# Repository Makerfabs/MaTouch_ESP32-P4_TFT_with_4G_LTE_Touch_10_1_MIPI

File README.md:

# MaTouch ESP32-P4 TFT with 4G LTE Touch 10.1“ MIPI

## Introduction

The MaTouch ESP32-P4 TFTTouch 10.1" MIPI with 4G LTE SIM7670G is an upgraded high-resolution, all-in-one HMI solution designed for smart control systems, industrial dashboards, remote IoT terminals, and AI-enabled applications. This module integrates a powerful ESP32-P4 processor, built-in SIM7670G 4G LTE Cat.1 module, a crystal-clear 10.1" IPS display, full multimedia support, and robust multi-mode wired/wireless connectivity, all inside a refined, ready-to-use enclosure.

Powered by the RISC-V dual-core ESP32-P4 (400MHz) with 16MB Flash and 32MB PSRAM, the system handles complex UIs, LVGL rendering, and real-time multimedia tasks with ease. The independent ESP32-C6 wireless module adds Wi-Fi 6 and Bluetooth LE support for reliable, modern IoT connectivity, while the onboard 4G LTE module enables stable data transmission without local Wi-Fi or Ethernet coverage.

One of the standout features is the stunning 10.1-inch 1280×800 IPS MIPI display, offering sharp visuals, vibrant colors, and smooth touch interaction—ideal for both consumer-facing interfaces and professional industrial panels.Integrated 2MP MIPI camera (SC2336) delivers high-definition image capture, suitable for facial recognition, monitoring, visual interaction, and embedded AI vision tasks. With onboard microphone input, the device is also well-prepared for far-field voice control or audio-enabled applications. For stable and high-speed communication, the device features built-in Ethernet (IP101GRI)—making it suitable for industrial environments where wireless alone is not reliable.A refined protective enclosure allows developers to deploy the device quickly without additional mechanical design. Each unit also comes with a MicroSD card pre-included, enabling logs, multimedia storage, and rapid local data processing right out of the box.

Product Link: [MaTouch ESP32-P4 TFT with 4G LTE Touch 10.1“ MIPI](https://www.makerfabs.com/matouch-esp32-p4-tfttouch-10-1-mipi-with-4g-lte-sim7670g.html)

Wiki Link:  [MaTouch ESP32-P4 TFT with 4G LTE Touch 10.1“ MIPI](https://wiki.makerfabs.com/MaTouch%20ESP32_P4%20TFT%20with%204G%20LTE%20Touch%2010.1%E2%80%9C%20MIPI.html)

Example：1.[4G_LTE_HTTP_Test](https://github.com/Makerfabs/MaTouch_ESP32-P4_TFT_with_4G_LTE_Touch_10_1_MIPI#4g_lte_http_test)

## Features

- Controller: ESP32-P4NRW32X
- Flash: 16MB Flash
- PSRAM: 32MB
- Wireless: 2.4GHz Wi-Fi 6 (802.11ax)，Bluetooth® 5 (LE)(ESP32-C6FH4)
- LCD: 10.1", 1280x800 resolution
- LCD Driver: JD9365
- LCD interface: MIPI
- Touch Panel: 5 Points Touch, Capacitive
- Touch Panel Driver: GT911
- USB: 1 * USB to UART, 1 * USB_NATIVE, 1 * USB_CDC/JTAG, 1 * USB_OTG, 1 * USB_DEVICE,
- Power Supply: USB Type-C 5.0V(4.0V~5.25V)
- Button: Flash button and reset button
- Camera Maximum Resolution: 2 Million Pixels, 1920H×1080V
- Camera Driver: SC2336
- Camera interface: MIPI
- Ethernet: IP101GRI
- 4G LTE: SIM7670G
- 4G Category: TDD/FDD-LTE CAT.1
- Data rate: 10 Mbps (DL),5 Mbps (UL)
- LTE-FDD Bands: B1/B2/B3/B4/B5/B7/B8/B12/B13/B18 /B19/B20/B25/B26/B28/B66/B71
- LTE-TDD Bands: B34/B38/B39/B40/B41
- Microphone input: Yes
- Audio output: ES8311
- MicroSD: Yes
- Charger: Yes
- Battery Connector: Yes
- Expansion interface: 26 * GPIO
- Arduino support: Yes
- LVGL support: Yes

## Example

### 4G_LTE_HTTP_Test

For details of this example, please refer to the [Wiki](https://wiki.makerfabs.com/MaTouch%20ESP32_P4%20TFT%20with%204G%20LTE%20Touch%2010.1%E2%80%9C%20MIPI.html#54g_lte_http) document.

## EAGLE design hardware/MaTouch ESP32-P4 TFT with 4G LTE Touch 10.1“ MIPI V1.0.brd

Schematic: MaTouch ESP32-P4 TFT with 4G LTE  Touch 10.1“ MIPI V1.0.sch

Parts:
1V8, 3V: TEST-POINT'4545'; TP-D45MIL; PARTNO DNP
BAT: JST-2P; HW2-SMD-2.0-90D
BAT1: CR1220SMT; CR1220-SMD
BOOT: TS24CA; 2*4*3.5MM
BOOT1: MOMENTARY-SWITCH-SPST-SMD-6.0X3.5MM; TACTILE_SWITCH_SMD_6.0X3.5MM
C1, C93, C94, C95, C96, C121, C124, C125, C126, C127, C128, C129, C130, C135, C140, C141: 1uF/16V; 0603
C2: 10pF/50V; DISCRETE_C0603
C3, C4, C6, C10, C16, C23, C29, C46, C54: 10uF; DISCRETE_C0603
C5, C21, C22, C28, C31, C34, C35, C42, C43, C48, C62, C65, C71, C74, C76, C78, C80, C83, C89, C97, C102, C107, C110, C114, C137, C142, C152, C165, C168, C170, C172, C174, C176, C178, C180, C182, C191, C193, C196, C220, C225, C227: 10uF; 0603
C6_BOOT, C6_RST: MOMENTARY-SWITCH-SPST-SMD-4.6X2.8MM; TACTILE_SWITCH_SMD_4.6X2.8MM
C6_EN, C6_IO9, C6_U0RXD, C6_U0TXD: PAD-TEST-POINT-CIRCLE'4545'; TP_4545; PARTNO DNP
C7, C8, C14, C17, C18, C19, C24, C26, C30, C32, C47, C60, C66, C108, C158, C185: 0.1uF; DISCRETE_C0603
C9, C51, C67, C72, C73, C75, C77, C79, C81, C84, C90, C91, C92, C98, C99, C100, C103, C104, C105, C106, C109, C111, C115, C131, C132, C138, C139, C143, C145, C147, C150, C153, C154, C155, C166, C169, C171, C173, C175, C177, C179, C181, C183, C192, C200, C203, C207, C209, C221, C222, C223, C224, C226: 0.1uF; 0603
C11: 4.7uF/35V; DISCRETE_C1206
C12: 0.1uF/50V; DISCRETE_C0603
C13: NC; DISCRETE_C0603
C15: 100nF; DISCRETE_C0603
C20, C25, C27, C41, C64, C136, C184: 4.7uF/16V; 0603
C33, C148, C149: 330pF/50V; 0603
C45, C53, C55, C205: NC; 0603
C49, C50, C63, C101, C194, C197, C206, C208: 1uF; 0603
C52: 1nF; 0603
C61, C190, C199, C202, C219: 33pF; 0603
C68: NC; DISCRETE_C1206
C69, C70, C116, C117: 12pF; DISCRETE_C0402
C82: 10nF; 0603
C85, C86: 20pF; DISCRETE_C0603
C87, C88: 15pF; DISCRETE_C0603
C118, C119, C120, C122, C123, C133, C134, C144, C146, C151, C167: 22pF; 0603
C156, C157: 1nF/50V; 0603
C159: 100nF; C0402
C160, C161: 10uF; C0603
C162, C163: 33pF; C0603
C164: 100nF; C0603
C195, C204: 100uF; EIA3528
C198: 100pF; 0603
C201: 10pF; 0603
C210, C211, C212: 22pF_NC; 0603
CHRG: RED; CHIPLED_0805_NOOUTLINE
CSI_RST: MOMENTARY-SWITCH-SPST-SMD-4.6X2.8MM; TACTILE_SWITCH_SMD_4.6X2.8MM
D1: 1N4148WS; SOD323
D2, D7, D13: 0603ESDA-05N; DISCRETE_SOD523
D3, D8: 5.1V; SOD-323
D4, D10: SMF05C; SOT363
D5, D12: SS54; DO-214AC
D6: B5819WS; SOD323
D+: TEST-POINT'4545'; TP-D45MIL; PARTNO DNP
D-: TEST-POINT'4545'; TP-D45MIL; PARTNO DNP
DONE: GREEN; CHIPLED_0805_NOOUTLINE
FB1, FB2, FB3, FB4, FB5: INDUCTORFB-30OHM; 0603
GPS: ANTENNA-U-FL; 4P-U-FL
IO34, IO35, IO36, IO37, IO38: TEST-POINT'4545'; TP-D45MIL; PARTNO DNP
J1, J2: GROVE-CONNECTOR-SMD'90D'; HW4-SMD-2.0-90D
J3: XH2.54-2P
J4: FPC-24P; SMD26-50P-1760L450W
J6, J10: CON2X20-254P-A; SMD2X20-254P-5080L750W920H
J7: HR961160C
J8: CON31-30P-A; SMD31-30P-1090L320W100H
L1: 10µH/±30%; CR54
L2: 4.7µH/±20%/3A; SRN6045
L3, L4: 2.2µH/±30%/3.4A; CR54
L5: BLM18BD252SN1; L0603
L6: 68nH; L0603
L7: 10µH/±20%/3.2A; CR54
LTE: ANTENNA-U-FL; 4P-U-FL
M1, M2, M3, M4, M5, M6, M7, M8, M9: M2.5
MIC: SAO-3729-M-42-008; MIC4-SMD-3.76X2.95MM
NET: NET; CHIP-LED0805
P1: DEBUG6; DEBUG*6
P2, P4: AFC01-S06FCC-00; SMD8-50P-740L535W
PWK: MOMENTARY-SWITCH-SPST-SMD-6.0X3.5MM; TACTILE_SWITCH_SMD_6.0X3.5MM
PWR: GREEN; CHIPLED_0805_NOOUTLINE
PWR1: JS102011JAQN; SMD-6-2.5MM
Q1, Q5, Q6, Q10, Q13, Q16, Q21, Q24: MOSFET-PCHANNEL; SOT23-3
Q2: 32.768K; XTAL3215
Q3, Q4, Q7: S8050; SOT23
Q8, Q9, Q11, Q12, Q14, Q15, Q17, Q18, Q22, Q23, Q25, Q26, Q27, Q28: 600mA/40V; SOT23-3
Q19, Q20: BS138; SOT23
Q29, Q32: BC847C; SOT23
Q30, Q31, Q33, Q34, Q35, Q36: 2N7002; SOT23
R1, R39, R44, R58, R60, R69, R70, R108, R156, R157, R158, R159, R172, R174, R176, R180, R191, R193: 10K; DISCRETE_R0603
R2, R17, R35, R41, R56, R63, R64, R68, R74, R75, R76, R77, R78, R79, R80, R81, R82, R83, R84, R89, R90, R91, R92, R93, R94, R96, R97, R98, R99, R100, R102, R109, R124, R125, R126, R127, R128, R129, R133, R134, R135, R136, R137, R144, R147, R153, R154, R155, R163, R167, R168, R170, R171, R184, R185, R217, R232, R235: 0R; R0603
R3, R46, R196: NC; R0603
R4, R6, R7, R8, R9, R55, R57, R173, R175, R177, R181, R186, R187, R188, R189, R190, R192, R194, R195: 51K; DISCRETE_R0603
R5, R31, R36, R37, R42, R47, R149, R160, R161: NC; DISCRETE_R0603
R10: 33K; R0603
R11, R24: 200K; R0603
R12, R13, R14, R15, R27, R38, R51, R53, R72, R73: 5.1K; DISCRETE_R0603
R16, R22, R25, R26, R66, R139, R143, R151, R164, R222, R224, R226, R228: 10K; R0603
R18, R67, R145: 100K; R0603
R19: 1.2K; DISCRETE_R0603
R20, R21, R40, R45, R54, R65, R71, R85, R86, R101, R110, R111, R112: 33R; R0603
R23: 50R; DISCRETE_R0603
R29, R218, R238: 1.2K; R0603
R30, R34, R103, R104, R105, R106, R107, R219: 100R; R0603
R32, R33: 3.6R; DISCRETE_R0603
R43, R169: 499K/NC; R0603
R48, R182: 3.3K; R0603
R49, R200, R215, R220: 47K; R0603
R50: 680K; R0603
R52: 470K; R0603
R59: 4.7K; DISCRETE_R0603
R87, R178, R179: 1.5K; R0603
R88: 1.5K/NC; R0603
R95, R150: 4.02K; R0603
R113, R116, R118, R120, R122, R123, R210, R211: 5.1K; R0603
R114, R115, R117, R119, R130: NC/5.1K; R0603
R121: 6.19K; R0603
R131, R132: NC/10K; R0603
R138: 10K/NC; R0603
R140: 200R; R0603
R141: 10R; R0603
R142: 0R/NC; R0603
R146: 22.1K; R0603
R148, R152, R162, R183, R197, R198: 2.2K; R0603
R165, R166, R244: 150K; R0603
R199, R214: 4.7K; R0603
R207, R208, R209, R212, R213: 22R; R0603
R216, R230, R231: 1K; R0603
R221, R223, R225, R227: 30K; R0603
R236, R237: 0.4R; 1206
R239: 50K; R0603
R240: 3R; R0603
R241, R242: 0.1R; DISCRETE_R2512
R243: 5.76K; R0603
RST: TS24CA; 2*4*3.5MM
RX: TEST-POINT'4545'; TP-D45MIL; PARTNO DNP
SD: HOLDER-MICROSD-9P; 9P-SMD-W/-RING
SIM: MICROSIM
SPK: 1X2P; 1X2P-SMT1.25MM
STA: NET; CHIP-LED0805
TX: TEST-POINT'4545'; TP-D45MIL; PARTNO DNP
U1: ESP32-C6-MINI-1
U2: RY3730; SOT23-6
U3: CH340K; ESOP-10-EP-150MIL
U4: MP2143DJ-LF-Z; TSOT23-8
U5, U10, U14, U15, U16: SPX3819; SOT23-5
U7: AMS1117-3.3V; SOT89
U8: ESP32-P4; QFN105-35P-500L500W
U9: W25Q128JV; SOIC-8-208MIL
U11, U17: TLV62569DBVR; SOT23-5-95P-300L300W
U12: ES8311; QFN20-40P-300L300W55H
U13: IP101GRI; QFN32-40P-400W400L
U18: A7670G
U19: TP5100; QFN17-65P-400L400W80H
U20: NS4150B; MSOP8-65P-490L300W110H
UN: PAD-TEST-POINT-CIRCLE'4545'; TP_4545; PARTNO DNP
UP: PAD-TEST-POINT-CIRCLE'4545'; TP_4545; PARTNO DNP
USB-CDC/JTAG: USB_C5; USB-C-16P-5
USB-DEVICE: USB_C5; USB-C-16P-5
USB-LTE: USB_C5; USB-C-16P-5
USB-NATIVE: USB_C5; USB-C-16P-5
USB-OTG: USB_C5; USB-C-16P-5
USB-TTL: USB_C5; USB-C-16P-5
VPWR: PAD-TEST-POINT-CIRCLE'4545'; TP_4545; PARTNO DNP
X1: 40MHz(10ppm); NX3225
X2: 25MHz(10ppm); NX3225
X3: 24MHz; OSC4-SMD-2.5X2.0X0.8MM

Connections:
1.8V: 1V8.T, C208.2, C209.2, D6.+, Q33.1 (G), Q34.1 (G), Q35.1 (G), Q36.1 (G), R222.2, R224.2, R226.2, R228.2, U18.15 (VDD_EXT), U18.97 (NC)
3.3V: C5.1, C9.1, C16.2, C17.2, C22.1, C23.2, C24.2, C29.2, C30.2, P1.1, R1.2, R36.2, R42.2, R44.2, R47.2, R57.2, R63.2, R66.2, R67.2, R155.1, R186.2, R187.2, R188.2, R189.2, R190.2, U1.3 (3V3)
25M_XI: C117.2, U13.2 (X1), X2.3 (X2)
25M_XO: C116.1, U13.3 (X2), X2.1 (X1)
+3V3: C3.2, C18.2, C19.2, C20.1, C25.1, C27.1, C42.1, C46.2, C47.2, C60.2, C66.2, C159.2, C184.1, C185.2, J1.3, J2.3, J8.1, J8.2, J8.3, J8.6, P2.5, P4.1, PWR.A, R22.2, R48.2, R63.1, R149.2, R151.2, R156.2, R182.2, R217.2, R221.2, R223.2, R225.2, R227.2, U3.7 (VCC), U3.10 (V3), U5.5 (VOUT), U14.1 (VIN), U14.3 (EN), U15.1 (VIN), U15.3 (EN), U16.1 (VIN), X3.1 (ENABLE), X3.4 (VDD)
A3V3: C137.1, C139.2, FB3.2, R133.2, U10.5 (VOUT)
ADCVREF: C126.2, R140.1, U12.15 (ADCVREF)
AGND: C118.2, C119.2, C120.2, C121.2, C126.1, C127.1, C128.2, C131.2, C132.2, C135.2, C140.2, C141.2, C142.2, C143.2, C144.2, C146.2, C148.2, C149.1, C161.1, C162.2, C163.2, C164.2, MIC.2 (GND), MIC.3 (GND), R137.1, R139.2, R163.1, R164.1, U12.5 (DGND), U12.10 (AGND), U12.21 (GND), U20.7 (GND)
ANT: C53.2, R64.1, U18.60 (RF_ANT)
AVDD: C121.1, R133.1, U12.11 (AVDD)
BAT: FB2.1, R141.1
BOOT: BOOT1.2, U18.6 (USB_BOOT)
C6_EN: C1.1, C6_EN.T, C6_RST.3 (2), C6_RST.4 (2), P1.6, R66.1, R171.2, U1.8 (EN)
C6_IO2: R68.1, U1.5 (IO2)
C6_U0RXD: C6_U0RXD.T, P1.4, U1.30 (RX0/IO17)
C6_U0TXD: C6_U0TXD.T, P1.3, U1.31 (TX0/IO16)
CCLK: C87.2, J4.14, R142.1, R144.1
CODEC_CE: R138.2, R139.1, U12.20 (CE)
COL: R119.2, R120.1, U13.4 (COL/RMII)
CRS: R115.2, R116.1, U13.20 (LEDMOD/CRS)
CSI_1V8: C31.1, C32.2, J4.16, R148.2, R183.2, R185.1, R197.2, R198.2, U15.5 (VOUT)
CSI_2V8: C21.1, C108.2, J4.23, J4.24, U14.5 (VOUT)
CSI_A_CLKN: J4.6, R104.2
CSI_A_CLKP: J4.7, R105.2
CSI_A_DATA0N: J4.9, R107.2
CSI_A_DATA0P: J4.10, R106.2
CSI_A_DATA1N: J4.3, R34.2
CSI_A_DATA1P: J4.4, R103.2
CSI_REXT: R150.1, U8.48 (CSI_REXT)
CSI_RST: C88.2, CSI_RST.3 (2), CSI_RST.4 (2), J4.17, R46.1, R147.2, R149.1
CSI_SCL: J4.21, Q20.2 (S), R183.1
CSI_SDA: J4.20, Q19.2 (S), R148.1
D+: U3.1 (UD+), USB-TTL.A6 (D+), USB-TTL.B6 (D+)
D-: U3.2 (UD-), USB-TTL.A7 (D-), USB-TTL.B7 (D-)
DACVREF: C127.2, U12.14 (DACVREF)
DSI_A_CLKN: J8.14, R98.1
DSI_A_CLKP: J8.15, R99.1
DSI_A_DATA0N: J8.11, R109.1
DSI_A_DATA0P: J8.12, R100.1
DSI_A_DATA1N: J8.17, R97.1
DSI_A_DATA1P: J8.18, R96.1
DSI_REXT: R95.1, U8.34 (DSI_REXT)
DTR: Q3.2 (E), R26.2, U3.4 (DTR#)
EAR_N: U18.41 (EAR_N)
EAR_P: U18.40 (EAR_P)
EN_DCDC: R196.1, U8.79 (EN_DCDC), U17.1 (EN)
ESP_EN: C8.2, Q4.3 (C), R16.1, RST.2, U8.103 (CHIP_PU)
FB_DCDC: C151.2, R43.1, R169.2, U8.78 (FB_DCDC), U17.5 (FB)
FLASH_CK_A: R93.1, U9.6 (CLK)
FLASH_CS_A: R89.1, R108.2, U9.1 (/CS)
FLASH_D_A: R94.1, U9.5 (DI(IO0))
FLASH_HD_A: R92.1, U9.7 (/HOLD/RESET(IO3))
FLASH_Q_A: R90.1, U9.2 (DO(IO1))
FLASH_WP_A: R91.1, U9.3 (/WP(IO2))
GND: BAT.3, BAT.4, BAT.- (2), BAT1.-, BOOT.1, BOOT.3, BOOT.4, C1.2, C2.1, C3.1, C4.1, C5.2, C6.1, C6_BOOT.1, C6_BOOT.2 (1), C6_RST.1, C6_RST.2 (1), C7.1, C8.1, C9.2, C10.1, C11.1, C12.1, C13.1, C14.1, C15.1, C16.1, C17.1, C18.1, C19.1, C20.2, C21.2, C22.2, C23.1, C24.1, C25.2, C26.1, C27.2, C28.2, C29.1, C30.1, C31.2, C32.1, C34.2, C35.1, C41.2, C42.2, C43.1, C45.2, C46.1, C47.1, C48.1, C49.1, C50.1, C51.1, C52.2, C53.1, C54.1, C55.1, C60.1, C62.1, C63.1, C64.2, C65.2, C66.1, C67.1, C69.2, C70.1, C71.2, C72.2, C73.2, C74.2, C75.2, C76.2, C77.2, C78.2, C79.2, C80.2, C81.2, C82.2, C83.2, C84.2, C85.2, C86.2, C87.1, C88.1, C89.2, C90.2, C91.2, C92.2, C93.2, C94.2, C95.2, C96.2, C97.2, C98.2, C99.2, C100.2, C101.2, C102.2, C103.2, C104.2, C105.2, C106.2, C107.2, C108.1, C109.2, C110.2, C111.2, C114.2, C115.2, C116.2, C117.1, C122.2, C123.2, C133.2, C134.2, C136.2, C137.2, C138.1, C139.1, C150.1, C152.2, C153.1, C154.2, C155.2, C156.2, C157.2, C159.1, C165.2, C166.1, C168.2, C169.1, C170.2, C171.2, C172.2, C173.2, C174.2, C175.2, C176.2, C177.2, C178.2, C179.2, C180.2, C181.2, C182.2, C183.2, C184.2, C185.1, C190.1, C191.2, C192.2, C193.1, C194.1, C195.C (-), C196.1, C197.1, C199.2, C200.1, C201.1, C202.1, C203.1, C204.C (-), C205.1, C206.1, C207.1, C208.1, C209.1, C210.1, C211.1, C212.1, C219.1, C220.2, C221.2, C222.2, C223.2, C224.2, C225.2, C226.2, C227.2, CSI_RST.1, CSI_RST.2 (1), D2.+, D3.A, D4.2 (A), D5.A, D7.+, D8.A, D10.2 (A), D13.+, GPS.GND1, GPS.GND2, GPS.GND3, J1.4, J1.SS1, J1.SS2, J2.4, J2.SS1, J2.SS2, J4.5, J4.8, J4.13, J4.15, J4.19, J4.22, J4.25, J4.26, J6.9, J6.10, J6.25, J6.26, J6.39, J6.40, J8.4, J8.7, J8.10, J8.13, J8.16, J8.19, J8.22, J8.23, J8.32, J8.33, J10.5, J10.6, J10.13, J10.14, J10.19, J10.20, J10.29, J10.30, J10.33, J10.34, LTE.GND1, LTE.GND2, LTE.GND3, M1.1, M2.1, M3.1, M4.1, M5.1, M6.1, M7.1, M8.1, M9.1, P1.2, P2.4, P2.7, P2.8, P4.2, P4.7, P4.8, PWK.1, Q7.2 (E), Q29.2 (S), Q30.2 (S), Q31.2 (S), Q32.2 (S), R10.1, R12.1, R13.1, R14.1, R15.1, R19.1, R27.1, R31.1, R32.1, R33.1, R37.2, R38.1, R49.1, R51.1, R52.1, R53.1, R58.1, R60.1, R70.1, R72.1, R73.1, R95.2, R113.1, R115.1, R117.1, R119.1, R121.1, R122.1, R131.1, R137.2, R146.1, R150.2, R159.1, R161.1, R169.1, R172.1, R173.1, R174.1, R175.1, R176.1, R177.1, R178.1, R180.1, R181.1, R191.1, R192.1, R193.1, R194.1, R195.1, R200.1, R210.1, R211.1, R215.1, R216.2, R220.1, R239.2, R243.1, RST.1, RST.3, RST.4, SD.6 (VSS), SD.G1, SD.G2, SD.G3, SD.G4, SIM.5 (GND), SPK.3, SPK.4, U1.1 (GND), U1.2 (GND), U1.11 (GND), U1.14 (GND), U1.36 (GND), U1.37 (GND), U1.38 (GND), U1.39 (GND), U1.40 (GND), U1.41 (GND), U1.42 (GND), U1.43 (GND), U1.44 (GND), U1.45 (GND), U1.46 (GND), U1.47 (GND), U1.48 (GND), U1.49.1 (GND), U1.49.2 (GND), U1.49.3 (GND), U1.49.4 (GND), U1.49.5 (GND), U1.49.6 (GND), U1.49.7 (GND), U1.49.8 (GND), U1.49.9 (GND), U1.50 (GND), U1.51 (GND), U1.52 (GND), U1.53 (GND), U2.2 (GND), U3.3 (GND), U3.EP, U4.4 (PGND), U4.6 (AGND), U5.2 (GND), U7.1 (GND), U8.105 (GND), U8.106 (GND), U8.107 (GND), U8.108 (GND), U8.109 (GND), U8.110 (GND), U8.111 (GND), U8.112 (GND), U8.113 (GND), U9.4 (GND), U10.2 (GND), U11.2 (GND), U13.33 (EP), U14.2 (GND), U15.2 (GND), U16.2 (GND), U17.2 (GND), U18.2 (GND), U18.17 (GND), U18.18 (GND), U18.29 (GND), U18.39 (GND), U18.45 (GND), U18.46 (GND), U18.54 (GND), U18.58 (GND), U18.59 (GND), U18.61 (GND), U18.62 (GND), U18.63 (GND), U18.64 (GND), U18.65 (GND), U18.69 (GND), U18.70 (GND), U18.71 (GND), U18.72 (GND), U18.73 (GND), U18.74 (GND), U18.75 (GND), U18.76 (GND), U18.77 (GND), U18.78 (GND), U18.79 (GND), U18.80 (GND), U18.81 (GND), U18.82 (GND), U18.83 (GND), U18.84 (GND), U18.85 (GND), U18.86 (GND), U18.87 (GND), U18.88 (GND), U18.89 (GND), U18.91 (GND), U18.92 (GND), U18.94 (GND), U19.7 (GND), U19.17 (EP), USB-CDC/JTAG.GND, USB-CDC/JTAG.GND2 (GND), USB-DEVICE.GND, USB-DEVICE.GND2 (GND), USB-LTE.GND, USB-LTE.GND2 (GND), USB-LTE.SHLD1 (SHLD), USB-LTE.SHLD2 (SHLD), USB-LTE.SHLD3 (SHLD), USB-LTE.SHLD4 (SHLD), USB-LTE.SHLD5 (SHLD), USB-LTE.SHLD6 (SHLD), USB-LTE.SHLD7 (SHLD), USB-LTE.SHLD8 (SHLD), USB-NATIVE.GND, USB-NATIVE.GND2 (GND), USB-OTG.GND, USB-OTG.GND2 (GND), USB-TTL.GND, USB-TTL.GND2 (GND), X1.2 (G2), X1.4 (G1), X2.2 (G2), X2.4 (G1), X3.2 (GND)
GNSS_PWR_EN: U18.20 (MK_IN_3), U18.98 (NC)
I2C_SCL: C134.1, P2.1, P4.4, Q20.3 (D), R42.1, R154.2, R182.1, U12.1 (CCLK)
I2C_SDA: C133.1, P2.2, P4.3, Q19.3 (D), R47.1, R48.1, R153.2, U12.19 (CDATA)
I2S_ASDOUT: R76.1, U12.7 (ASDOUT)
I2S_DSDIN: R74.1, U12.9 (DSDIN)
I2S_LRCK: C120.1, R75.1, U12.8 (LRCK)
I2S_MCLK: C118.1, R78.1, U12.2 (MCLK)
I2S_SCLK: C119.1, R77.1, U12.6 (SCLK)
IO0: C85.1, J6.23, J6.24, Q2.P$1 (1), U8.104 (GPIO0)
IO1: C86.1, J10.21, J10.22, Q2.P$2 (2), R142.2, U8.1 (GPIO1)
IO2: J6.21, J6.22, Q36.3 (D), R46.2, R227.1, U8.2 (GPIO2)
IO3: J1.1, J6.19, J6.20, U8.3 (GPIO3)
IO4: J1.2, J10.17, J10.18, U8.4 (GPIO4)
IO5: J10.15, J10.16, U8.5 (GPIO5)
IO6: J6.15, J6.16, R68.2, U8.6 (GPIO6)
IO7: J6.3, J6.4, R153.1, U8.7 (GPIO7)
IO8: J6.5, J6.6, R154.1, U8.8 (GPIO8)
IO9: R74.2, U8.10 (GPIO9)
IO9/BOOT: C6_BOOT.3 (2), C6_BOOT.4 (2), C6_IO9.T, P1.5, U1.23 (IO9)
IO10: R75.2, U8.11 (GPIO10)
IO11: R76.2, U8.12 (GPIO11)
IO12: R77.2, U8.13 (GPIO12)
IO12/USB_N: U1.17 (USB_D-/IO12), UN.T
IO13: R78.2, U8.14 (GPIO13)
IO13/USB_P: U1.18 (USB_D+/IO13), UP.T
IO14: R79.2, U8.15 (GPIO14)
IO15: R80.2, U8.16 (GPIO15)
IO16: R81.2, U8.17 (GPIO16)
IO17: R82.2, U8.18 (GPIO17)
IO18: R83.2, U8.19 (GPIO18)
IO19: R84.2, U8.20 (GPIO19)
IO20: J2.1, J6.13, J6.14, U8.22 (GPIO20)
IO21: J2.2, J6.11, J6.12, U8.23 (GPIO21)
IO22: J10.11, J10.12, R35.1, U8.24 (GPIO22)
IO23: J6.7, J6.8, R3.1, R59.2, U8.25 (GPIO23)
IO24: R101.1, U8.52 (GPIO24)
IO25: R110.1, U8.53 (GPIO25)
IO26: J6.31, J6.32, R111.1, U8.55 (GPIO26)
IO27: J10.37, J10.38, R112.1, U8.56 (GPIO27)
IO28: U8.57 (GPIO28), U13.19 (FX_HEN/CRS_DV/RXDV)
IO29: U8.58 (GPIO29), U13.18 (RXD0)
IO30: U8.60 (GPIO30), U13.17 (RXD1)
IO31: R88.1, U8.61 (GPIO31), U13.22 (MDC)
IO32: J10.25, J10.26, Q35.3 (D), R225.1, U8.63 (GPIO32)
IO33: J6.29, J6.30, R214.2, U8.64 (GPIO33)
IO34: IO34.T, U8.65 (GPIO34), U13.9 (TXD0)
IO35: BOOT.2, IO35.T, Q3.3 (C), R22.1, U8.66 (GPIO35), U13.8 (TXD1)
IO36: IO36.T, J10.23, J10.24, R151.1, U8.68 (GPIO36)
IO37: IO37.T, J10.7, J10.8, R17.1, U8.69 (GPIO37)
IO38: IO38.T, J10.9, J10.10, R2.1, U8.70 (GPIO38)
IO45: J10.39, J10.40, R71.1, U8.87 (GPIO45)
IO46: J10.35, J10.36, R199.2, U8.88 (GPIO46)
IO47: J6.37, J6.38, Q33.3 (D), R221.1, U8.89 (GPIO47)
IO48: J6.33, J6.34, Q34.3 (D), R223.1, U8.90 (GPIO48)
IO49: U8.92 (GPIO49), U13.5 (TXEN)
IO50: U8.93 (GPIO50), U13.10 (TXCLK/50M_CLKI), U13.14 (RXCLK/50M_CLKO)
IO51: R131.2, R132.1, U8.94 (GPIO51), U13.32 (RESET_N)
IO52: R87.1, U8.95 (GPIO52), U13.23 (MDIO)
IO53: J6.35, J6.36, R170.1, U8.97 (GPIO53)
IO54: J10.31, J10.32, R171.1, U8.98 (GPIO54)
LCD_RST: C15.2, J8.5, R1.1
LCD_VDD: C26.2, C28.1, R157.2, R158.2, R160.2, R185.2, U16.5 (VOUT)
LED+: C11.2, C12.2, C68.2, D1.-, D+.T, J3.1, J8.29, J8.30, J8.31, U2.5 (OVP)
LED-: C68.1, D-.T, J3.2, J8.24, J8.25, J8.26, J8.27, R32.2, R33.2, U2.3 (FB)
LTE_DTR: Q36.2 (S), R228.1, U18.3 (DTR)
LTE_RI: Q35.2 (S), R226.1, U18.4 (RI)
LTE_RXD: Q34.2 (S), R224.1, U18.10 (RXD)
LTE_TXD: Q33.2 (S), R222.1, U18.9 (TXD)
LTE_USB_DN: R213.1, U18.28 (USB_DM)
LTE_USB_DP: R212.1, U18.27 (USB_DP)
MF_GNSS_RXD: R230.2, U18.49 (UART3_RXD)
MF_GNSS_TXD: R231.2, U18.50 (UART3_TXD)
MICN: C130.2, R162.1, R163.2
MICP: C129.2, C160.2, R152.1
MIC_N: U18.43 (MIC_N)
MIC_P: U18.42 (MIC_P)
MKF_3V1: C107.1, C109.1, U13.28 (REGOUT)
MKF_3V3: C71.1, C72.1, C73.1, C89.1, C90.1, C92.1, C99.1, C105.1, C106.1, C158.2, C161.2, C164.1, C167.1, C168.1, C169.2, FB1.2, FB4.1, J6.1, J6.2, J6.17, J6.18, L4.P$2 (2), MIC.1 (VDD), Q1.2 (S), R41.1, R69.2, R102.1, R136.1, R138.1, R145.2, R155.2, U8.9 (VDD_LP), U8.21 (VDD_IO_0), U8.62 (VDD_IO_4), U8.75 (VDD_LDO), U8.77 (VDD_DCDCC), U8.96 (VDD_IO_6), U8.101 (VDD_ANA)
MKF_LDO_VO1: C93.1, R56.1, U8.71 (VDDO_FLASH)
MKF_LDO_VO2: C94.1, C97.1, C98.1, U8.59 (VDD_PSRAM_0), U8.67 (VDD_PSRAM_1), U8.72 (VDDO_PSRAM)
MKF_LDO_VO3: C78.1, C79.1, C95.1, C101.1, U8.41 (VDD_MIPI_DPHY), U8.73 (VDDO_3)
MKF_LDO_VO4: C54.2, C96.1, C102.1, C103.1, R4.2, R5.2, R6.2, R7.2, R8.2, R9.2, U8.74 (VDDO_4), U8.85 (VDD_IO_5)
MKF_VBAT: C83.1, C84.1, FB2.2, FB4.2, R16.2, U8.102 (VDD_BAT)
MKF_VDD_HP: C74.1, C75.1, C91.1, C104.1, C151.1, C152.1, C153.2, L3.P$2 (2), R43.2, U8.26 (VDD_HP_0), U8.76 (VDD_HP_2), U8.91 (VDD_HP_3)
unnamed: L2.1, U4.3 (SW)
unnamed: Q4.1 (B), R26.1
unnamed: Q3.1 (B), R25.1
unnamed: C61.1, R10.2, R11.1, U4.7 (FB)
unnamed: R38.2, USB-CDC/JTAG.A5 (CC1)
unnamed: R15.2, USB-NATIVE.A5 (CC1)
unnamed: PWR.C, R19.2
unnamed: R18.1, U4.1 (PG)
unnamed: R24.1, U4.8 (EN)
unnamed: R13.2, USB-TTL.A5 (CC1)
unnamed: R12.2, USB-TTL.B5 (CC2)
unnamed: Q29.1 (G), R30.1, R49.2
unnamed: NET.A, R29.1
unnamed: R14.2, USB-NATIVE.B5 (CC2)
unnamed: NET.C, Q29.3 (D)
unnamed: C55.2, R64.2, R184.1
unnamed: D1.+, L1.P$2 (2), R23.2, U2.1 (LX)
unnamed: R27.2, USB-CDC/JTAG.B5 (CC2)
unnamed: D13.-, LTE.D, R184.2
unnamed: R53.2, USB-OTG.A5 (CC1)
unnamed: C34.1, C150.2, R41.2, R196.2, U17.4 (VIN)
unnamed: C2.2, R23.1
unnamed: L3.P$1 (1), U17.3 (SW)
unnamed: Q7.3 (C), R31.2, R39.1, U2.4 (EN)
unnamed: R51.2, USB-OTG.B5 (CC2)
unnamed: Q22.1 (B), Q22.3 (C), Q23.1 (B), R191.2
unnamed: Q21.1 (G), Q23.3 (C), R192.2
unnamed: R67.1, U1.22 (IO8)
unnamed: Q7.1 (B), R59.1, R60.2
unnamed: R73.2, USB-DEVICE.A5 (CC1)
unnamed: C158.1, Q1.1 (G), R69.1, R70.2, R71.2
unnamed: R72.2, USB-DEVICE.B5 (CC2)
unnamed: R144.2, X3.3 (OUT)
unnamed: R156.1, U16.3 (EN)
unnamed: BAT1.+$1 (+), BAT1.+$2 (+1), R141.2
unnamed: C160.1, C163.1, L5.2
unnamed: C130.1, U12.17 (MIC1N)
unnamed: C162.1, L5.1, MIC.4 (OUT)
unnamed: C167.2, R145.1, R146.2, U11.5 (FB)
unnamed: C122.1, C125.1, U12.12 (OUTP)
unnamed: R17.2, U3.9 (RXD)
unnamed: C123.1, C124.1, U12.13 (OUTN)
unnamed: C124.2, R134.1
unnamed: R2.2, U3.8 (TXD)
unnamed: C125.2, R135.1
unnamed: C129.1, U12.18 (MIC1P)
unnamed: C131.1, C132.1, R136.2, U12.3 (PVDD), U12.4 (DVDD)
unnamed: C135.1, R140.2, R152.2, R162.2
unnamed: C140.1, U20.2 (BYPASS)
unnamed: C141.1, C142.1, C143.1, FB5.1, U20.6 (VCC)
unnamed: C145.2, R165.1
unnamed: C147.2, R166.1
unnamed: C33.2, C149.2, R168.2, SPK.2
unnamed: C33.1, C148.1, R167.2, SPK.1
unnamed: R143.1, U11.1 (EN)
unnamed: Q11.1 (B), Q11.3 (C), Q12.1 (B), R174.2
unnamed: L4.P$1 (1), U11.3 (SW)
unnamed: R89.2, U8.27 (FLASH_CS)
unnamed: R90.2, U8.28 (FLASH_Q)
unnamed: R91.2, U8.29 (FLASH_WP)
unnamed: Q8.1 (B), Q8.3 (C), Q9.1 (B), R172.2
unnamed: R92.2, U8.31 (FLASH_HOLD)
unnamed: R93.2, U8.32 (FLASH_CK)
unnamed: R94.2, U8.33 (FLASH_D)
unnamed: C154.1, J7.6 (CT2)
unnamed: R96.2, U8.35 (DSI_DATAP1)
unnamed: R97.2, U8.36 (DSI_DATAN1)
unnamed: R98.2, U8.37 (DSI_CLKN)
unnamed: R99.2, U8.38 (DSI_CLKP)
unnamed: R100.2, U8.39 (DSI_DATAP0)
unnamed: C45.1, U5.4 (BYP)
unnamed: C155.1, J7.5 (CT1)
unnamed: C80.1, C81.1, C82.1, R102.2, U8.51 (VDD_USBPHY)
unnamed: C156.1, J7.10 (CGND)
unnamed: C157.1, J7.13, J7.14
unnamed: J7.11 (LED-), R178.2
unnamed: R103.1, U8.47 (CSI_DATAP1)
unnamed: R34.1, U8.46 (CSI_DATAN1)
unnamed: R104.1, U8.45 (CSI_CLKN)
unnamed: R105.1, U8.44 (CSI_CLKP)
unnamed: R106.1, U8.43 (CSI_DATAP0)
unnamed: R107.1, U8.42 (CSI_DATAN0)
unnamed: R109.2, U8.40 (DSI_DATAN0)
unnamed: J7.2 (LED1-), R179.1
unnamed: Q5.1 (G), Q9.3 (C), R173.2
unnamed: Q10.1 (G), Q12.3 (C), R175.2
unnamed: Q14.1 (B), Q14.3 (C), Q15.1 (B), R176.2
unnamed: Q13.1 (G), Q15.3 (C), R177.2
unnamed: Q17.1 (B), Q17.3 (C), Q18.1 (B), R180.2
unnamed: Q16.1 (G), Q18.3 (C), R181.2
unnamed: Q30.1 (G), R199.1, R200.2
unnamed: Q25.1 (B), Q25.3 (C), Q26.1 (B), R193.2
unnamed: Q24.1 (G), Q26.3 (C), R194.2
unnamed: Q6.1 (G), Q28.3 (C), R195.2
unnamed: Q20.1 (G), R198.1
unnamed: R124.1, U8.80 (GPIO39)
unnamed: R125.1, U8.81 (GPIO40)
unnamed: R126.1, U8.82 (GPIO41)
unnamed: R127.1, U8.83 (GPIO42)
unnamed: R128.1, U8.84 (GPIO43)
unnamed: Q19.1 (G), R197.1
unnamed: R129.1, U8.86 (GPIO44)
unnamed: Q27.1 (B), Q27.3 (C), Q28.1 (B), R58.2
unnamed: R207.1, U18.31 (USIM1_DATA)
unnamed: R208.1, U18.32 (USIM1_CLK)
unnamed: R209.1, U18.33 (USIM1_RST)
unnamed: R211.2, USB-LTE.A5 (CC1)
unnamed: R210.2, USB-LTE.B5 (CC2)
unnamed: R212.2, USB-LTE.A6 (D+), USB-LTE.B6 (D+)
unnamed: R213.2, USB-LTE.A7 (D-), USB-LTE.B7 (D-)
unnamed: Q31.1 (G), R214.1, R215.2
unnamed: BOOT1.1, R216.1
unnamed: C199.1, L6.1, R217.1
unnamed: C198.1, GPS.D, L6.2
unnamed: C198.2, U18.90 (NC)
unnamed: Q32.1 (G), R219.1, R220.2
unnamed: R218.1, STA.A
unnamed: Q32.3 (D), STA.C
unnamed: R230.1, U18.95 (NC)
unnamed: R231.1, U18.96 (NC)
unnamed: C219.2, D6.-, U18.116 (NC)
unnamed: C220.1, C221.1, R236.1, R237.1, R238.1, U19.1 (VIN1), U19.4 (VIN2), U19.5 (VIN3), U19.16 (VIN4)
unnamed: CHRG.A, DONE.A, R238.2
unnamed: CHRG.C, U19.15 (!CHRG)
unnamed: DONE.C, U19.14 (!STDBY)
unnamed: C222.1, R244.2, U19.10 (VREG)
unnamed: R239.1, U19.12 (PTRICK)
unnamed: D5.C, L7.P$1 (1), R240.1, U19.2 (LX1), U19.3 (LX2)
unnamed: C224.1, C225.1, L7.P$2 (2), R241.1, R242.1, U19.8 (VS)
unnamed: R243.2, R244.1, U19.11 (TS)
unnamed: C223.1, R240.2
NETLED: R30.2, U18.52 (NETLIGHT)
NRST: D2.-, Q31.3 (D), U18.16 (RESET)
OUTN: C146.1, C147.1, R134.2
OUTP: C144.1, C145.1, R135.2
PA_CTRL: R164.2, R170.2, U20.1 (CTRL)
PA_INL+: R165.2, U20.3 (IN+)
PA_INL-: R166.2, U20.4 (IN-)
PA_OUTL+: R167.1, U20.8 (OUT+)
PA_OUTL-: R168.1, U20.5 (OUT-)
PHY_3V3: C110.1, C111.1, C114.1, C115.1, FB1.1, J7.1 (LED1+), R87.2, R88.2, R114.2, R116.2, R118.2, R120.2, R123.2, R130.2, R132.2, U13.13 (VDD_IO), U13.31 (AVDD33)
PHY_AD0: R123.1, R179.2, U13.11 (LED0/PHY_AD0)
PHY_AD3: J7.12 (LED+), R122.2, U13.12 (LED3/PHY_AD3)
PHY_ISET: R121.2, U13.25 (ISET)
PHY_TESTON: R130.1, U13.24 (TEST_ON)
PWRKEY: C205.2, PWK.2, Q30.3 (D), U18.1 (PWRKEY)
RD+: J7.7 (RD+), U13.27 (MDI_RP)
RD-: J7.8 (RD-), U13.26 (MDI_RN)
RESET: R147.1
RTS: Q4.2 (E), R25.2, U3.6 (RTS#)
RXER: R117.2, R118.1, U13.21 (INTR_32/RXER)
SD1_CLK: D4.5 (C4), R5.1, R128.2, SD.5 (SCLK)
SD1_CMD: D4.3 (C2), R4.1, R129.2, SD.3 (DI)
SD1_D0: D4.6 (C5), R6.1, R124.2, SD.7 (DO)
SD1_D1: R9.1, R125.2, SD.8 (DATA1)
SD1_D2: D4.1 (C1), R7.1, R126.2, SD.1 (DATA2)
SD1_D3: R8.1, R127.2, SD.2 (CS)
SD1_VDD: C10.2, C14.2, D4.4 (C3), Q1.3 (D), R55.1, SD.4 (VDD)
SD2_CLK: R83.1, R186.1, U1.25 (SDIO_CLK/IO19)
SD2_CMD: R57.1, R84.1, U1.24 (SDIO_CMD/IO18)
SD2_D0: R79.1, R187.1, U1.26 (SDIO_D0/IO20)
SD2_D1: R80.1, R188.1, U1.27 (SDIO_D1/IO21)
SD2_D2: R81.1, R189.1, U1.28 (SDIO_D2/IO22)
SD2_D3: R82.1, R190.1, U1.29 (SDIO_D3/IO23)
SD_DET: R55.2, SD.9 (CDN)
SHLR: R159.2, R160.1
SIM_CLK: C211.2, D10.4 (C3), R208.2, SIM.3 (CLK)
SIM_DATA: C212.2, D10.3 (C2), R207.2, SIM.7 (I/O)
SIM_RST: C210.2, D10.5 (C4), R209.2, SIM.2 (RST)
SIM_VDD: C190.2, C200.2, D10.6 (C5), SIM.1 (VCC), U18.30 (USIM1_VDD)
STATUS: R219.2, U18.66 (STATUS)
STBYB: R157.1
TD+: J7.3 (TD+), U13.30 (MDI_TP)
TD-: J7.4 (TD-), U13.29 (MDI_TN)
TP_INT: P2.3, P4.5, R3.2, R36.1, R37.1
TP_RST: C13.2, P2.6, P4.6, R35.2, R44.1
TXER: R113.2, R114.1, U13.1 (TXER/FXSD)
UART_LOG_RX: RX.T, U18.22 (UART_LOG_RX)
UART_LOG_TX: TX.T, U18.23 (UART_LOG_TX)
UPDN: R158.1, R161.2
USB1P1_N: R45.2, R101.2
USB1P1_N_2: R65.2, R111.2
USB1P1_P: R40.2, R110.2
USB1P1_P_2: R54.2, R112.2
USB1_5V: C170.1, C171.1, Q5.3 (D), Q8.2 (E), USB-NATIVE.VBUS1 (VBUS), USB-NATIVE.VBUS2 (VBUS)
USB1_D+: R20.1, USB-NATIVE.A6 (D+), USB-NATIVE.B6 (D+)
USB1_D-: R21.1, USB-NATIVE.A7 (D-), USB-NATIVE.B7 (D-)
USB2_5V: C172.1, C173.1, Q10.3 (D), Q11.2 (E), USB-CDC/JTAG.VBUS1 (VBUS), USB-CDC/JTAG.VBUS2 (VBUS)
USB2_D+: R40.1, USB-CDC/JTAG.A6 (D+), USB-CDC/JTAG.B6 (D+)
USB2_D-: R45.1, USB-CDC/JTAG.A7 (D-), USB-CDC/JTAG.B7 (D-)
USB3_5V: C174.1, C175.1, Q13.3 (D), Q14.2 (E), USB-OTG.VBUS1 (VBUS), USB-OTG.VBUS2 (VBUS)
USB3_D+: R54.1, USB-OTG.A6 (D+), USB-OTG.B6 (D+)
USB3_D-: R65.1, USB-OTG.A7 (D-), USB-OTG.B7 (D-)
USB4_5V: D12.C, Q6.2 (S), Q28.2 (E), USB-DEVICE.VBUS1 (VBUS), USB-DEVICE.VBUS2 (VBUS)
USB4_D+: R85.1, USB-DEVICE.A6 (D+), USB-DEVICE.B6 (D+)
USB4_D-: R86.1, USB-DEVICE.A7 (D-), USB-DEVICE.B7 (D-)
USB_5V: C178.1, C179.1, Q5.2 (S), Q9.2 (E), Q10.2 (S), Q12.2 (E), Q13.2 (S), Q15.2 (E), Q16.2 (S), Q18.2 (E), Q21.3 (D), Q22.2 (E), R236.2, R237.2
USB_DM: R21.2, R86.2, U8.49 (DM)
USB_DP: R20.2, R85.2, U8.50 (DP)
VBAT: BAT.+ (1), C180.1, C181.1, C226.1, C227.1, Q24.3 (D), Q25.2 (E), R241.2, R242.2, U19.9 (BAT)
VBAT_ADC: C52.1, R50.1, R52.2, U18.51 (VBAT_ADC)
VBAT_IN: R50.2
VBUS: C4.2, C6.2, C7.2, C176.1, C177.1, Q16.3 (D), Q17.2 (E), USB-TTL.VBUS1 (VBUS), USB-TTL.VBUS2 (VBUS)
VCC_5V: C41.1, C43.2, C51.2, C62.2, C63.2, C64.1, C67.2, C136.1, C138.2, C165.1, C166.2, C182.1, C183.1, D12.A, FB5.2, J10.1, J10.2, J10.3, J10.4, L1.P$1 (1), PWR1.3, PWR1.3@1 (3), Q6.3 (D), Q27.2 (E), R18.2, R24.2, R39.2, R143.2, U2.6 (IN), U4.2 (VIN), U5.1 (VIN), U5.3 (EN), U7.3 (IN), U10.1 (VIN), U10.3 (EN), U11.4 (VIN), VPWR.T
VDD: 3V.T, C65.1, C206.2, C207.2, FB3.1, U7.2 (OUT), U7.4 (OUT), U18.99 (VDD_AUX)
VDD_FLASH: C76.1, C77.1, C100.1, R56.2, R108.1, U8.30 (VDD_FLASHIO), U9.8 (VCC)
VIN: R232.2, R235.2
VMID: C128.1, U12.16 (VMID)
VPP: C35.2, D3.C, PWR1.2, PWR1.2@1 (2), Q21.2 (S), Q23.2 (E), Q24.2 (S), Q26.2 (E)
VUSB: C191.1, C192.1, U18.24 (VBUS), USB-LTE.VBUS1 (VBUS), USB-LTE.VBUS2 (VBUS)
V_BATT: C48.2, C49.2, C50.2, C61.2, C193.2, C194.2, C195.A (+), C196.2, C197.2, C201.2, C202.2, C203.2, C204.A (+), D7.-, D8.C, L2.2, R11.2, R29.2, R218.2, R232.1, R235.1, U4.5 (OUT), U18.55 (VBAT), U18.56 (VBAT), U18.57 (VBAT)
XTAL_N: C70.2, U8.99 (XTAL_N), X1.3 (X2)
XTAL_P: C69.1, U8.100 (XTAL_P), X1.1 (X1)

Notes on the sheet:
www.makerfabs.com
Design by Charlin
USB
LEDS
POWER AND FILTERING
USB TO SERIAL CONVERTER
MaTouch ESP32-P4 TFT with 4G LTE Touch 10.1" MIPI V1.0
POWER
USB to UART
USB Type C
TF Card
Closer to IC
Back Light
Mabee
MCU
ME6217
key flash
CMD
CLK
2.5~5.5V
Zener
Camera
SDA
GND
MCLK
D1N
D1P
CKN
CKP
D0N
D0P
1.8V
RST
SCL
2.8V
Level Shifter
Touch
MIPI_DP3
MIPI_DN3
MIPI_DP2

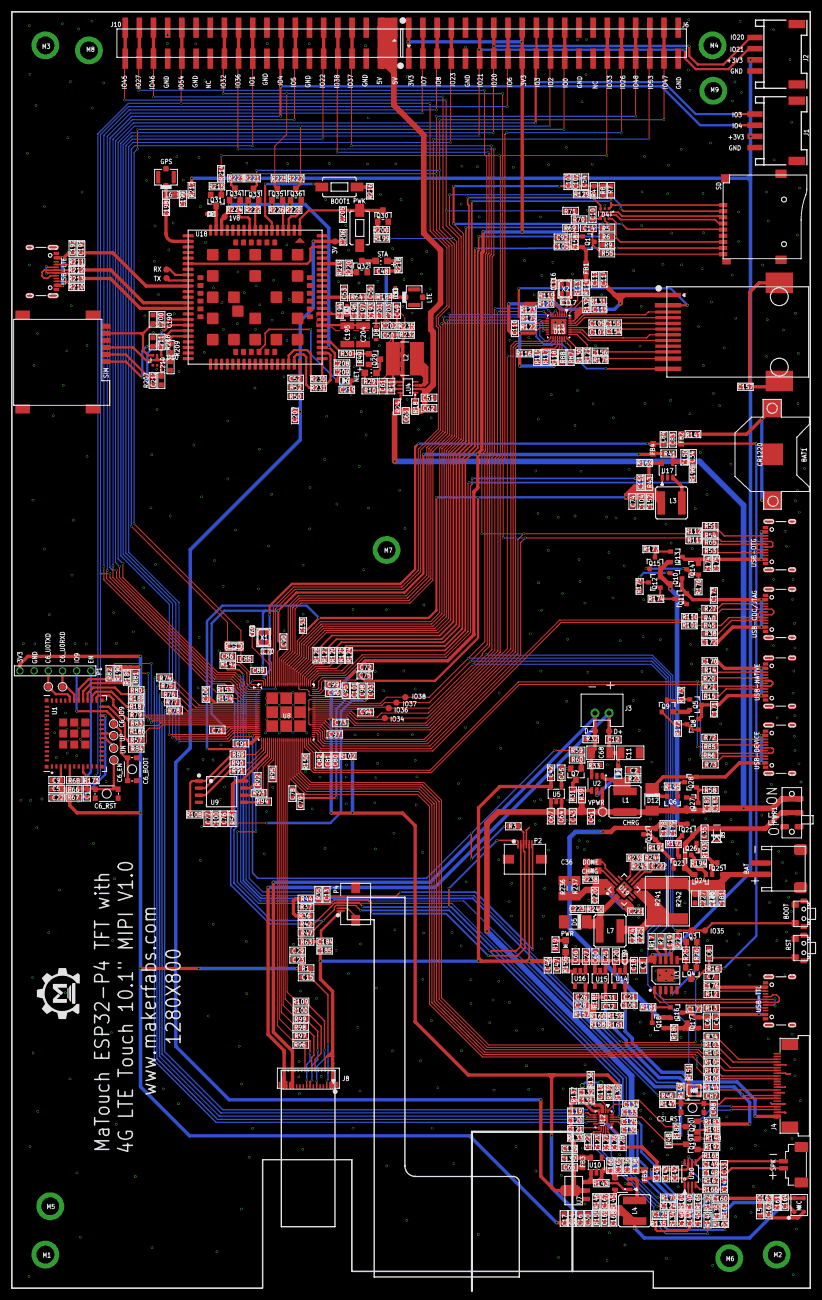
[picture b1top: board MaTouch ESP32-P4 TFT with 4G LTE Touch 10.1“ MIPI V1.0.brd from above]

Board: 2 copper layers, 143.0 x 228.6 mm, 584 parts (0 on the bottom side), 345 nets.

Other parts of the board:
U$1: MAKERFABS_0.3

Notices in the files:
parts and their libraries:
SparkFun-PowerSymbols: Licensing: Creative Commons ShareAlike 4.0 International - https://creativecommons.org/licenses/by-sa/4.0
microbuilder: This work is placed in the public domain, and may be freely used for commercial and non-commercial work with the following conditions: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
